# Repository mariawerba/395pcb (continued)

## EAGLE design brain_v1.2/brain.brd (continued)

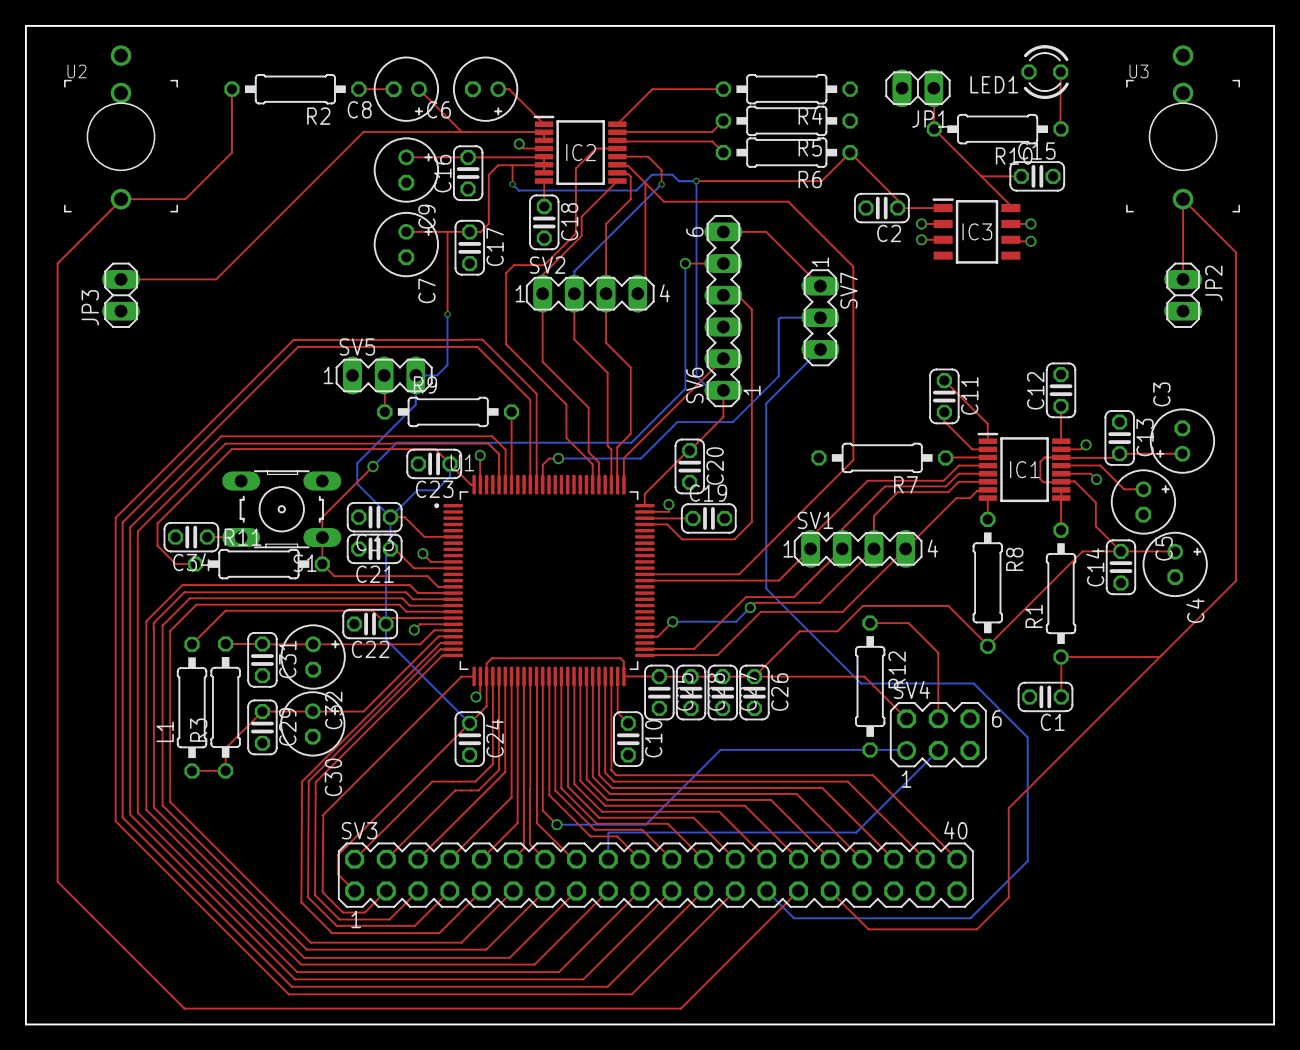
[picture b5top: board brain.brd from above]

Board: 2 copper layers, 100.0 x 80.0 mm, 65 parts (0 on the bottom side), 76 nets.

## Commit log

2020-01-01 add all v1 pcbs
